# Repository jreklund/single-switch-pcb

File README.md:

# Single MX Hotswap (Cherry)

Single MX Hotswap PCB for hand wiring dactyl-manuform keyboards and their derivatives.

- 17x18x1.6mm (W x L x H)
- 1N4148W diode (SMT or THT)
- Kailh MX Hotswap Socket
- 2 cols / 2 rows on each side
- 4 screw holes (M1.4)

Panelization and fabrication is made possible by [KiKit – Automation for KiCAD](https://github.com/yaqwsx/KiKit).

## Panelization

```
kikit panelize --layout "grid; rows: 5; cols: 5; space: 2mm" --tabs "annotation" --cuts "mousebites; drill: 0.5mm" --post "millradius: 1mm" pcb/single.kicad_pcb pcb/panel.kicad_pcb
```

## Fabrication (JLCPCB)

```
kikit fab jlcpcb pcb/panel.kicad_pcb pcb/out
```

## Credits

This model is based off [su120-keyboard](https://github.com/e3w2q/su120-keyboard) and it's stripped down [panel](https://github.com/kissetfall/su120-keyboard).

| Footprint | Author | Modification |
| --------- | ------ | ------- |
| 1pin_conn | [su120-keyboard](https://github.com/e3w2q/su120-keyboard) | Removed silkscreen.
| diod_TH_SMD | [su120-keyboard](https://github.com/e3w2q/su120-keyboard) | Top orientation only. Changed diode symbol.
| MX-Hotswap-1U | [MX_V2](https://github.com/ai03-2725/MX_V2) | 17x18mm (W x L). Added charm on left pad.

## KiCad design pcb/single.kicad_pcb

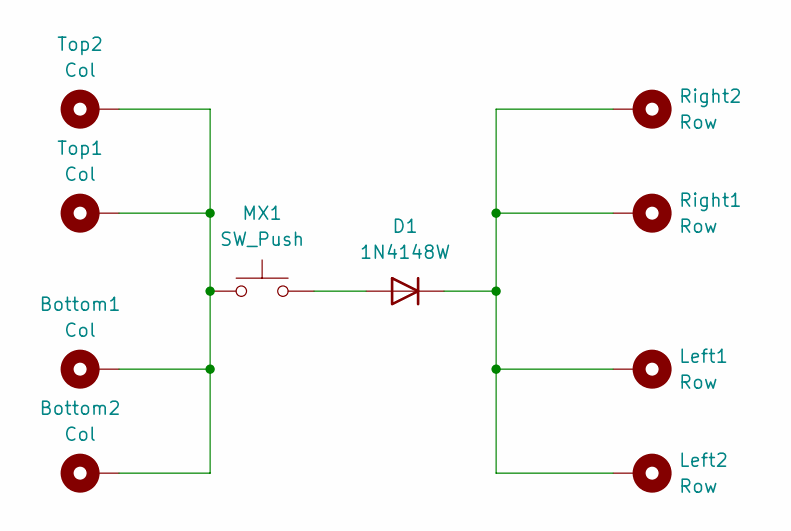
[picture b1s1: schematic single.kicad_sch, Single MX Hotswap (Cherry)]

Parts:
Bottom1, Bottom2: Col; 1pin_conn-mod
D1: 1N4148W; diode_TH_SMD-top
Left1, Left2: Row; 1pin_conn-mod
MX1: SW_Push; MX-Hotswap-17x18mm-charm
Right1, Right2: Row; 1pin_conn-mod
Top1, Top2: Col; 1pin_conn-mod

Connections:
unnamed: Bottom1.1, Bottom2.1, MX1.1, Top1.1, Top2.1
unnamed: D1.2 (A), MX1.2
unnamed: D1.1 (K), Left1.1, Left2.1, Right1.1, Right2.1

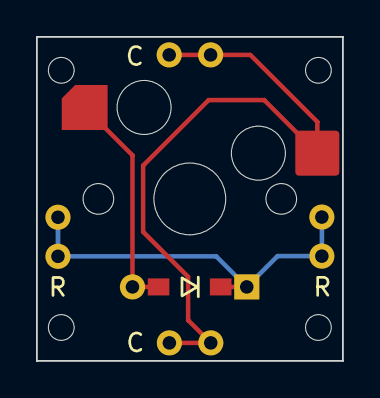
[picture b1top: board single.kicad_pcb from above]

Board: 2 copper layers, 17.0 x 18.0 mm, 10 parts (0 on the bottom side), 3 nets.

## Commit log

2025-01-05 Initial fabricated version
